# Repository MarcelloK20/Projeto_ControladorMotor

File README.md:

A pasta 'CodigoFinal' possui a última versão de código testada e que está presente no microcontrolador ATtiny85.
A pasta 'PCB_ControladorMotor' possui todos os arquivos do desenho da PCB e impressões 3D para parte estrutural.
O arquivo 'TesteFinal' contém a simulação do projeto desenvolvida no software Simulide.

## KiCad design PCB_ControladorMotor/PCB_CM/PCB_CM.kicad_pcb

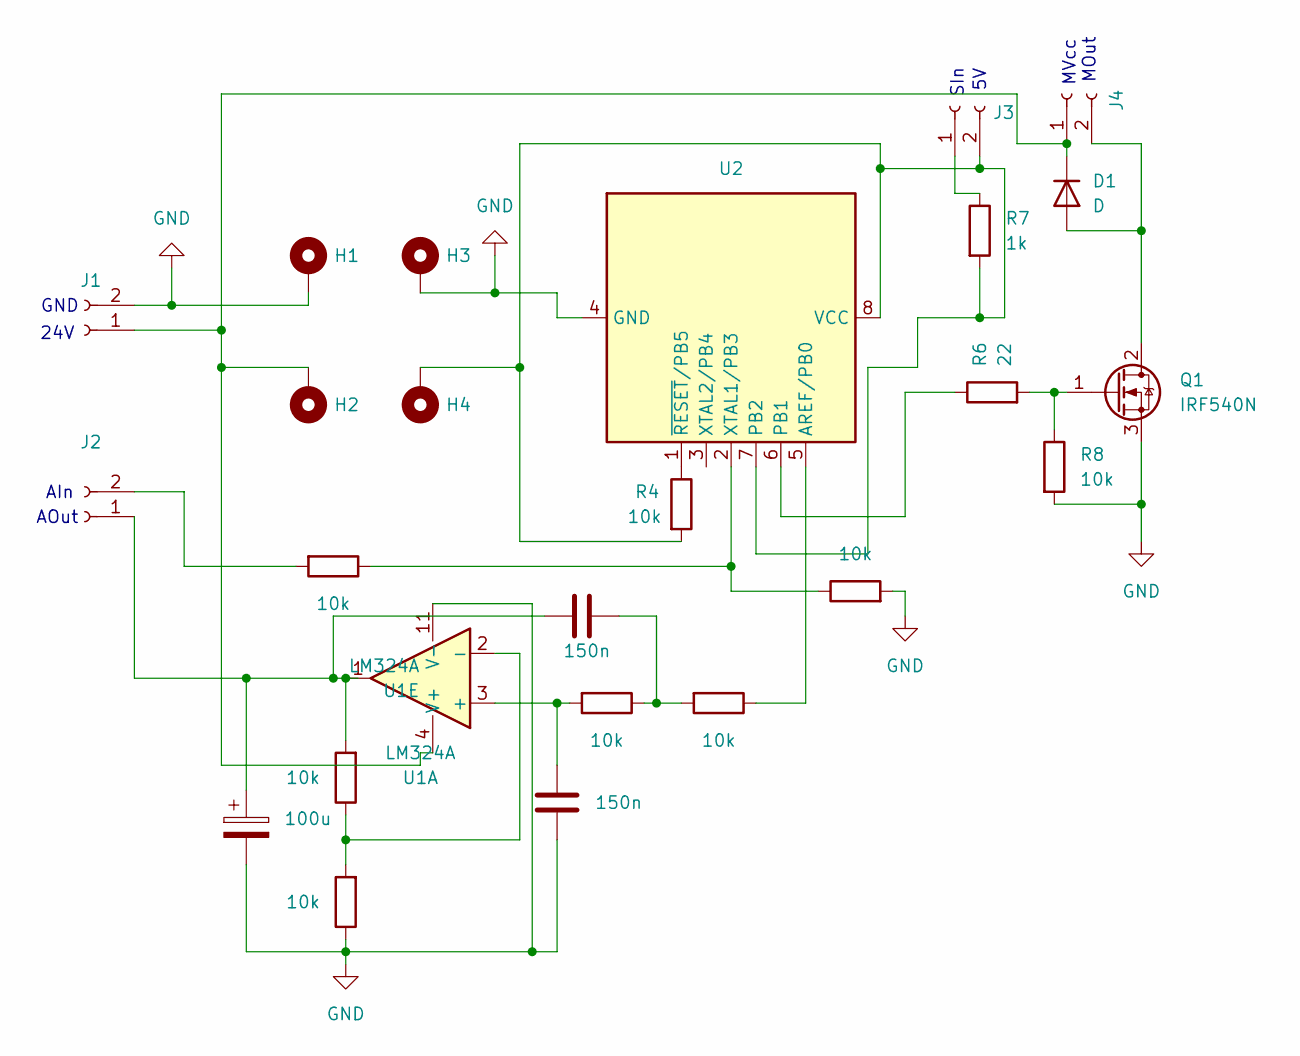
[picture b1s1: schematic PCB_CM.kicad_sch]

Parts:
C1: 100u; CP_Radial_D8.0mm_P5.00mm
C2, C3: 150n; C_Disc_D5.0mm_W2.5mm_P2.50mm
D1: D; D_5W_P5.08mm_Vertical_AnodeUp
H1, H2, H3, H4: MountingHole_Pad; MountingHole_2.2mm_M2_DIN965_Pad
J1, J2, J3, J4: Conn_01x02_Socket; PhoenixContact_MC_1,5_2-G-3.81_1x02_P3.81mm_Horizontal
Q1: IRF540N; TO-220-3_Vertical
R1, R2, R3, R4, R5, R8, R9, R10: 10k; R_Axial_DIN0207_L6.3mm_D2.5mm_P10.16mm_Horizontal
R6: 22; R_Axial_DIN0207_L6.3mm_D2.5mm_P10.16mm_Horizontal
R7: 1k; R_Axial_DIN0207_L6.3mm_D2.5mm_P10.16mm_Horizontal
U1: LM324A; SOIC-14_3.9x8.7mm_P1.27mm
U2: ATtiny85V-10P; DIP-8_W7.62mm

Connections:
GND: C1.2, C2.2, H1.1, H3.1, J1.2, Q1.3 (S), R2.1, R8.2, R10.2, U1.11 (V-), U2.4 (GND)
unnamed: C3.2, R3.1, R5.2
unnamed: D1.2 (A), J4.2, Q1.2 (D)
unnamed: D1.1 (K), H2.1, J1.1, J4.1, U1.4 (V+)
unnamed: C1.1, C3.1, J2.1, R1.2, U1.1
unnamed: J2.2, R9.2
unnamed: J3.1, R7.1
unnamed: H4.1, J3.2, R4.2, R7.2, U2.7 (PB2), U2.8 (VCC)
unnamed: Q1.1 (G), R6.2, R8.1
unnamed: C2.1, R3.2, U1.3 (+)
unnamed: R1.1, R2.2, U1.2 (-)
unnamed: R5.1, U2.5 (AREF/PB0)
unnamed: R6.1, U2.6 (PB1)
unnamed: R9.1, R10.1, U2.2 (XTAL1/PB3)
unnamed: R4.1, U2.1 (~RESET/PB5)

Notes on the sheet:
AIn
SIn
MVcc
MOut
GND
AOut
24V

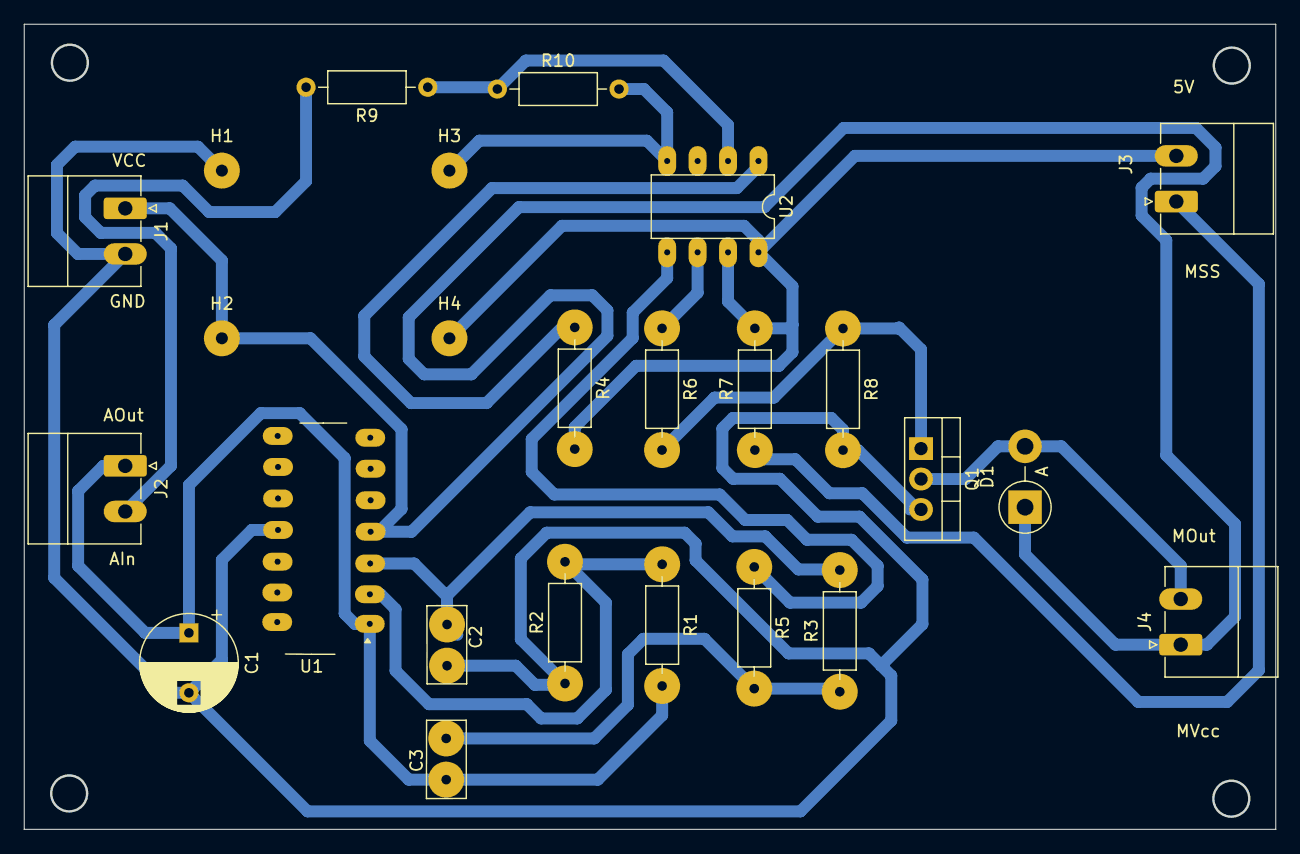
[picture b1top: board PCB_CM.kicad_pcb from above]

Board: 2 copper layers, 104.3 x 67.1 mm, 25 parts (0 on the bottom side), 15 nets.

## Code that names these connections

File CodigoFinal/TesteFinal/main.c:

#define F_CPU 1000000UL

#include <avr/io.h>
#include <util/delay.h>
#include <avr/interrupt.h>

#define MAX_RPM 5300
#define MAX_PWM 255
#define PULSES_PER_REV 28
volatile uint32_t count = 0;
volatile uint32_t pulse_count = 0;

void Timer1_init()
{
	// Definir o Timer1 em modo CTC
	TCCR1 |= (1 << CTC1) | (1 << CS13) | (1 << CS10);  // Prescaler de 256

	// Calcular o valor do OCR1C para 10ms
	OCR1C = 39;  // Para 1MHz: (1MHz / (256 * 100Hz)) - 1 = 38

	// Habilitar interrupção de comparação do Timer1
	TIMSK |= (1 << OCIE1A);
}

void Timer0_init()
{
	// Configurar o Timer0 para Fast PWM, modo não invertido
	TCCR0A |= (1<<COM0A1) | (1<<WGM00) | (1<<WGM01) | (1 << COM0B1);
	TCCR0B |= (1<<CS01);  // Prescaler de 8 para o Timer0
	// Inicializar o valor do PWM
	OCR0B = 0;
	// Configurar o PB0 e PB1 como saída
	DDRB |= (1 << PB0) | (1 << PB1);
}

ISR(INT0_vect)
{
	pulse_count++;  // Contar os pulsos do encoder
}

ISR(TIMER1_COMPA_vect)
{
	count++;
	if (count >= 100)  // 100 * 10ms = 1 segundo
	{
		// Calcular RPM
		cli();
		uint32_t temp = pulse_count;
		pulse_count = 0;
		sei();
		uint32_t rpm = (temp * 60) / PULSES_PER_REV;

		// Calcular o valor do PWM
		uint32_t pwm_value = (rpm * MAX_PWM) / MAX_RPM;
		if (pwm_value > MAX_PWM) {
			pwm_value = MAX_PWM;
		}
		OCR0A = pwm_value;  // Aplicar o PWM no PB0

		// Resetar contadores
		count = 0;
	}
}

void adc_init() {
	// Selecionar Vref = AVcc e selecionar o canal ADC3 (PB3)
	ADMUX = 0b00000011;
	
	// Habilitar o ADC, definir o prescaler para 64 (1MHz/64 = 15625Hz)
	ADCSRA = (1 << ADEN) | (1 << ADPS2) | (1 << ADPS1);
}

uint16_t adc_read() {
	// Iniciar a conversão
	ADCSRA |= (1 << ADSC);
	
	// Aguardar a conversão completar
	while (ADCSRA & (1 << ADSC));
	
	// Retornar o valor ADC (10 bits)
	return ADC;
}


int main(void) {
	adc_init();
	Timer1_init();
	Timer0_init();

	// Configurar PB2 (INT0) como entrada e ativar o pull-up interno
	DDRB &= ~(1 << PB2);
	PORTB |= (1 << PB2);

	// Configurar a interrupção externa no PB2 (INT0) para borda de subida
	MCUCR |= (1 << ISC00) | (1 << ISC01);  // Configura INT0 para borda de subida
	GIMSK |= (1 << INT0);  // Habilita a interrupção INT0

	// Habilitar interrupções globais
	sei();

	
	while (1) {
		// Ler o valor do ADC (0-1023)
		uint16_t adc_value = adc_read();
		
		// Converter o valor ADC para 0-255 (8 bits)
		uint8_t valor_motor = adc_value >> 2;  // Equivalente a dividir por 4
		
		// Definir o valor do PWM
		OCR0B = valor_motor;
	}
}
